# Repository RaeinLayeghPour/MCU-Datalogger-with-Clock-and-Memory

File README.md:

# MCU Datalogger with Clock and Memory

A microcontroller-based data logging system featuring a real-time clock (RTC) and external memory (EEPROM/SPI flash) to timestamp and store sensor readings for offline retrieval and analysis.

---

## Features

- Real-time timestamping via DS3231 (I²C RTC module)
- Data storage on external EEPROM or SPI flash memory
- Configurable sampling interval and data format
- Power-efficient design for long-term deployment
- Accessible serial interface for data download/monitoring

---

## Tech Stack & Hardware

- **MCU:** Arduino Uno / ATmega328P
- **RTC:** DS3231 module (I²C)
- **Memory:** External EEPROM or SPI flash (e.g., 24LC256, 25LC512)
- **Language:** Arduino C/C++
- **Interface:** Serial (USB) + I²C/SPI protocols

---

## How It Works

1. On boot, the MCU initializes the RTC and memory.
2. Sensor data (analog/digital) is sampled at configured intervals.
3. Each reading is timestamped using the RTC.
4. Records are stored sequentially in external memory.
5. Data can be retrieved via serial commands (e.g., `dump`, `clear`).

---

## Applications

- Remote environmental monitoring (e.g., temperature, humidity)
- Power data logging (voltage/current)
- Industrial sensing (vibration, pressure)
- Educational electronics and embedded systems projects

---

## 📬 Contact

Reach out if you’d like to collaborate or discuss enhancements:

- [LinkedIn](https://www.linkedin.com/in/raeinlp)
- Email: raeen.layegh2017@gmail.com

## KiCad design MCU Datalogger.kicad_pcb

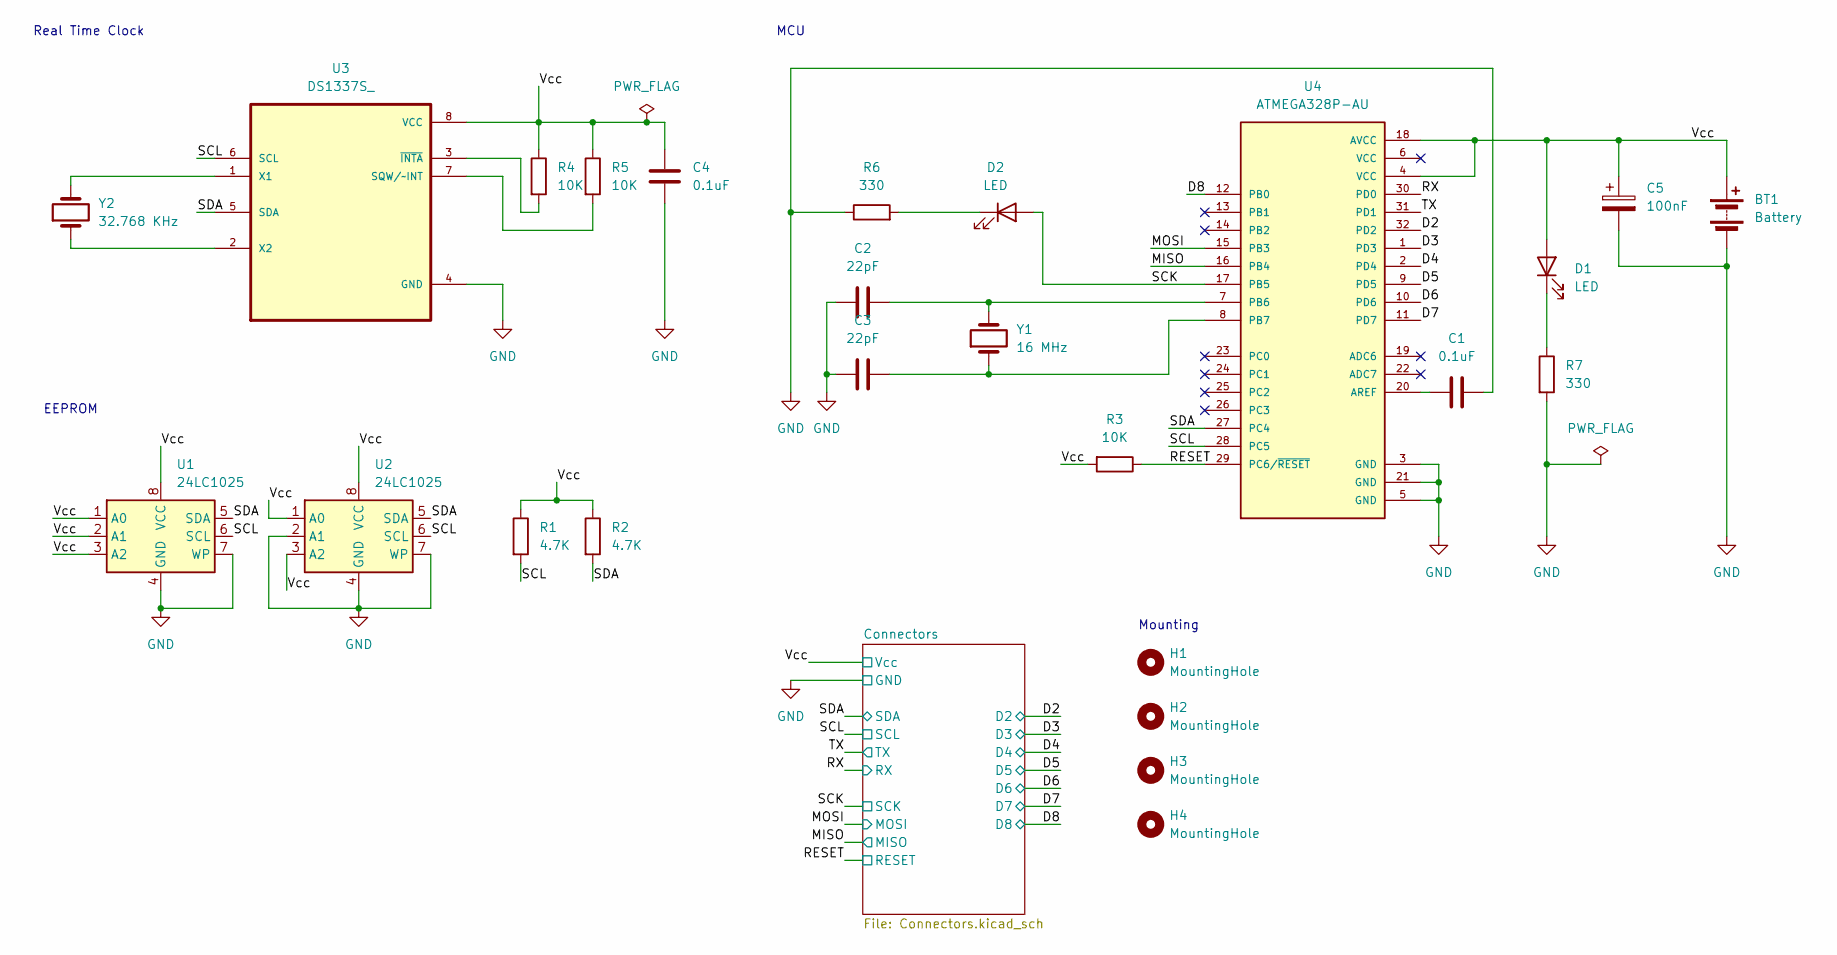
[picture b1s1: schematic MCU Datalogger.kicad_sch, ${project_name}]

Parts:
BT1: Battery; PinHeader_1x02_P2.54mm_Vertical
C1, C4: 0.1uF; C_0805_2012Metric
C2, C3: 22pF; C_0805_2012Metric
C5: 100nF; C_0805_2012Metric
D1, D2: LED; LED_0805_2012Metric
H1, H2, H3, H4: MountingHole; MountingHole_2.1mm
R1, R2: 4.7K; R_0805_2012Metric
R3, R4, R5: 10K; R_0805_2012Metric
R6, R7: 330; R_0805_2012Metric
U1, U2: 24LC1025; SSOP-8_5.25x5.24mm_P1.27mm
U3: DS1337S_; SOIC127P600X175-8N
U4: ATMEGA328P-AU; QFP80P900X900X120-32N; PARTREV 8271A
Y1: 16 MHz; Crystal_SMD_5032-2Pin_5.0x3.2mm_HandSoldering
Y2: 32.768 KHz; Crystal_SMD_5032-2Pin_5.0x3.2mm_HandSoldering

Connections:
/D2: U4.32 (PD2); also elsewhere on the board
/D3: U4.1 (PD3); also elsewhere on the board
/D4: U4.2 (PD4); also elsewhere on the board
/D5: U4.9 (PD5); also elsewhere on the board
/D6: U4.10 (PD6); also elsewhere on the board
/D7: U4.11 (PD7); also elsewhere on the board
/D8: U4.12 (PB0); also elsewhere on the board
/MISO: U4.16 (PB4); also elsewhere on the board
/MOSI: U4.15 (PB3); also elsewhere on the board
/RESET: R3.1, U4.29 (PC6/~RESET); also elsewhere on the board
/RX: U4.30 (PD0); also elsewhere on the board
/SCK: D2.2 (A), U4.17 (PB5); also elsewhere on the board
/SCL: R1.2, U1.6 (SCL), U2.6 (SCL), U3.6 (SCL), U4.28 (PC5); also elsewhere on the board
/SDA: R2.2, U1.5 (SDA), U2.5 (SDA), U3.5 (SDA), U4.27 (PC4); also elsewhere on the board
/TX: U4.31 (PD1); also elsewhere on the board
/Vcc: BT1.1 (+), C4.1, C5.1, D1.2 (A), R1.1, R2.1, R3.2, R4.1, R5.1, U1.1 (A0), U1.2 (A1), U1.3 (A2), U1.8 (VCC), U2.1 (A0), U2.3 (A2), U2.8 (VCC), U3.8 (VCC), U4.4 (VCC), U4.18 (AVCC); also elsewhere on the board
GND: BT1.2 (-), C1.2, C2.1, C3.1, C4.2, C5.2, R6.1, R7.2, U1.4 (GND), U1.7 (WP), U2.2 (A1), U2.4 (GND), U2.7 (WP), U3.4 (GND), U4.3 (GND), U4.5 (GND), U4.21 (GND); also elsewhere on the board
unnamed: D1.1 (K), R7.1
unnamed: D2.1 (K), R6.2
unnamed: R5.2, U3.7 (SQW/~INT)
unnamed: U3.1 (X1), Y2.2
unnamed: U3.2 (X2), Y2.1
unnamed: R4.2, U3.3 (~INTA)
unnamed: C1.1, U4.20 (AREF)
unnamed: C2.2, U4.7 (PB6), Y1.2
unnamed: C3.2, U4.8 (PB7), Y1.1

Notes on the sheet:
EEPROM
Mounting
MCU
Real Time Clock

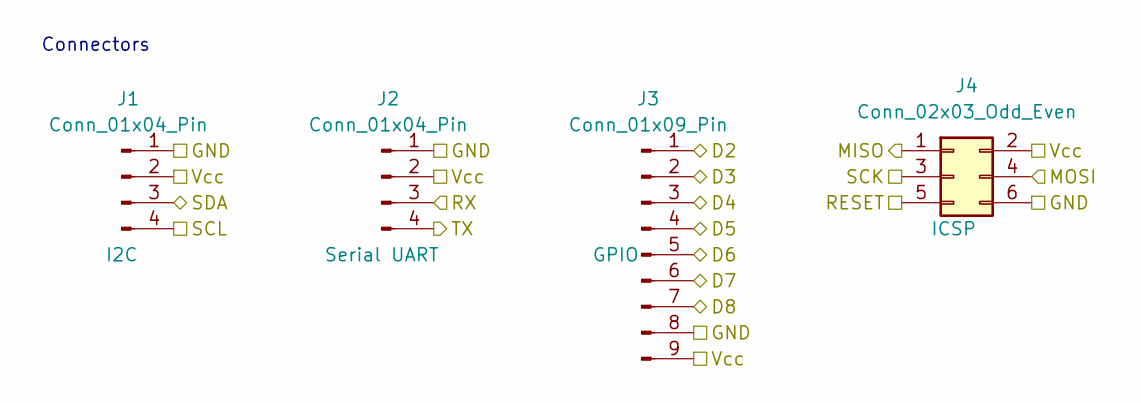
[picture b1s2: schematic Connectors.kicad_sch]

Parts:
J1, J2: Conn_01x04_Pin; PinHeader_1x04_P2.54mm_Vertical
J3: Conn_01x09_Pin; PinHeader_1x09_P2.54mm_Vertical
J4: Conn_02x03_Odd_Even; PinHeader_2x03_P2.54mm_Vertical

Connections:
/D2: J3.1; also elsewhere on the board
/D3: J3.2; also elsewhere on the board
/D4: J3.3; also elsewhere on the board
/D5: J3.4; also elsewhere on the board
/D6: J3.5; also elsewhere on the board
/D7: J3.6; also elsewhere on the board
/D8: J3.7; also elsewhere on the board
/MISO: J4.1; also elsewhere on the board
/MOSI: J4.4; also elsewhere on the board
/RESET: J4.5; also elsewhere on the board
/RX: J2.3; also elsewhere on the board
/SCK: J4.3; also elsewhere on the board
/SCL: J1.4; also elsewhere on the board
/SDA: J1.3; also elsewhere on the board
/TX: J2.4; also elsewhere on the board
/Vcc: J1.2, J2.2, J3.9, J4.2; also elsewhere on the board
GND: J1.1, J2.1, J3.8, J4.6; also elsewhere on the board

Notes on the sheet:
Connectors

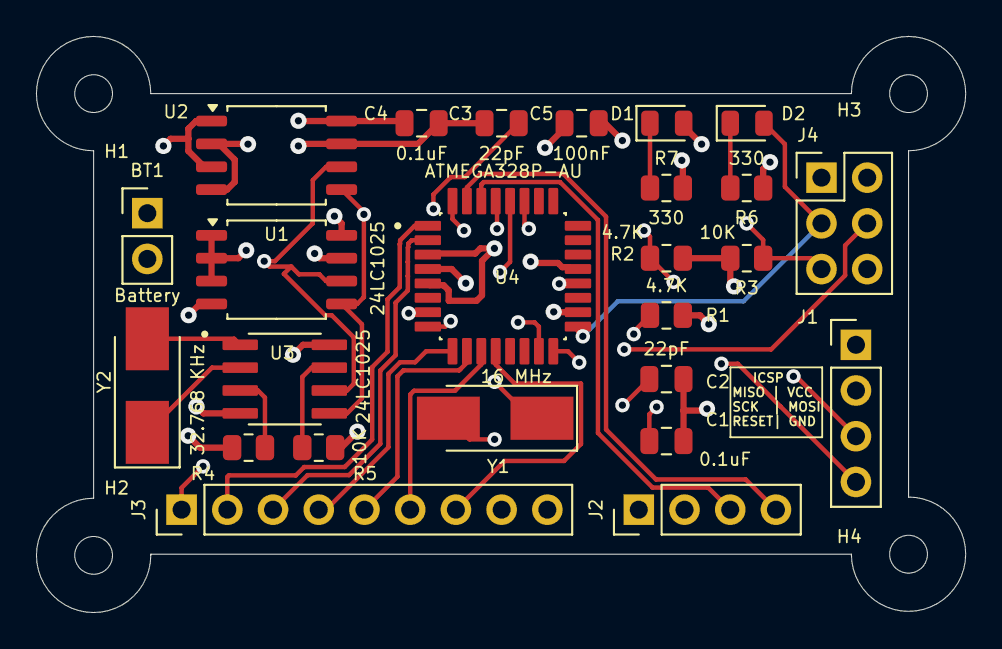
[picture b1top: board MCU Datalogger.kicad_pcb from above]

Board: 4 copper layers, 51.6 x 32.0 mm, 29 parts (0 on the bottom side), 26 nets.

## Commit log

2025-07-06 First commit of new project.
2025-07-06 Setup of EEschema for new project.
2025-07-06 Have added required symbols to the schematic sheets.
2025-07-06 Changed locations of symbols (arrange).
2025-07-06 Added component values.
2025-07-07 Completed symbol-footprint associations.
2025-07-07 Completed wiring of main sheet.
2025-07-07 Completed wiring in the second sheet.
2025-07-07 Allocated GND and Vcc nets to the power net class.
2025-07-07 Completed comments.
2025-07-07 Setup Pcbnew.
2025-07-07 Completed placement of footprints.
2025-07-08 Routing sans GND Vcc complete.
